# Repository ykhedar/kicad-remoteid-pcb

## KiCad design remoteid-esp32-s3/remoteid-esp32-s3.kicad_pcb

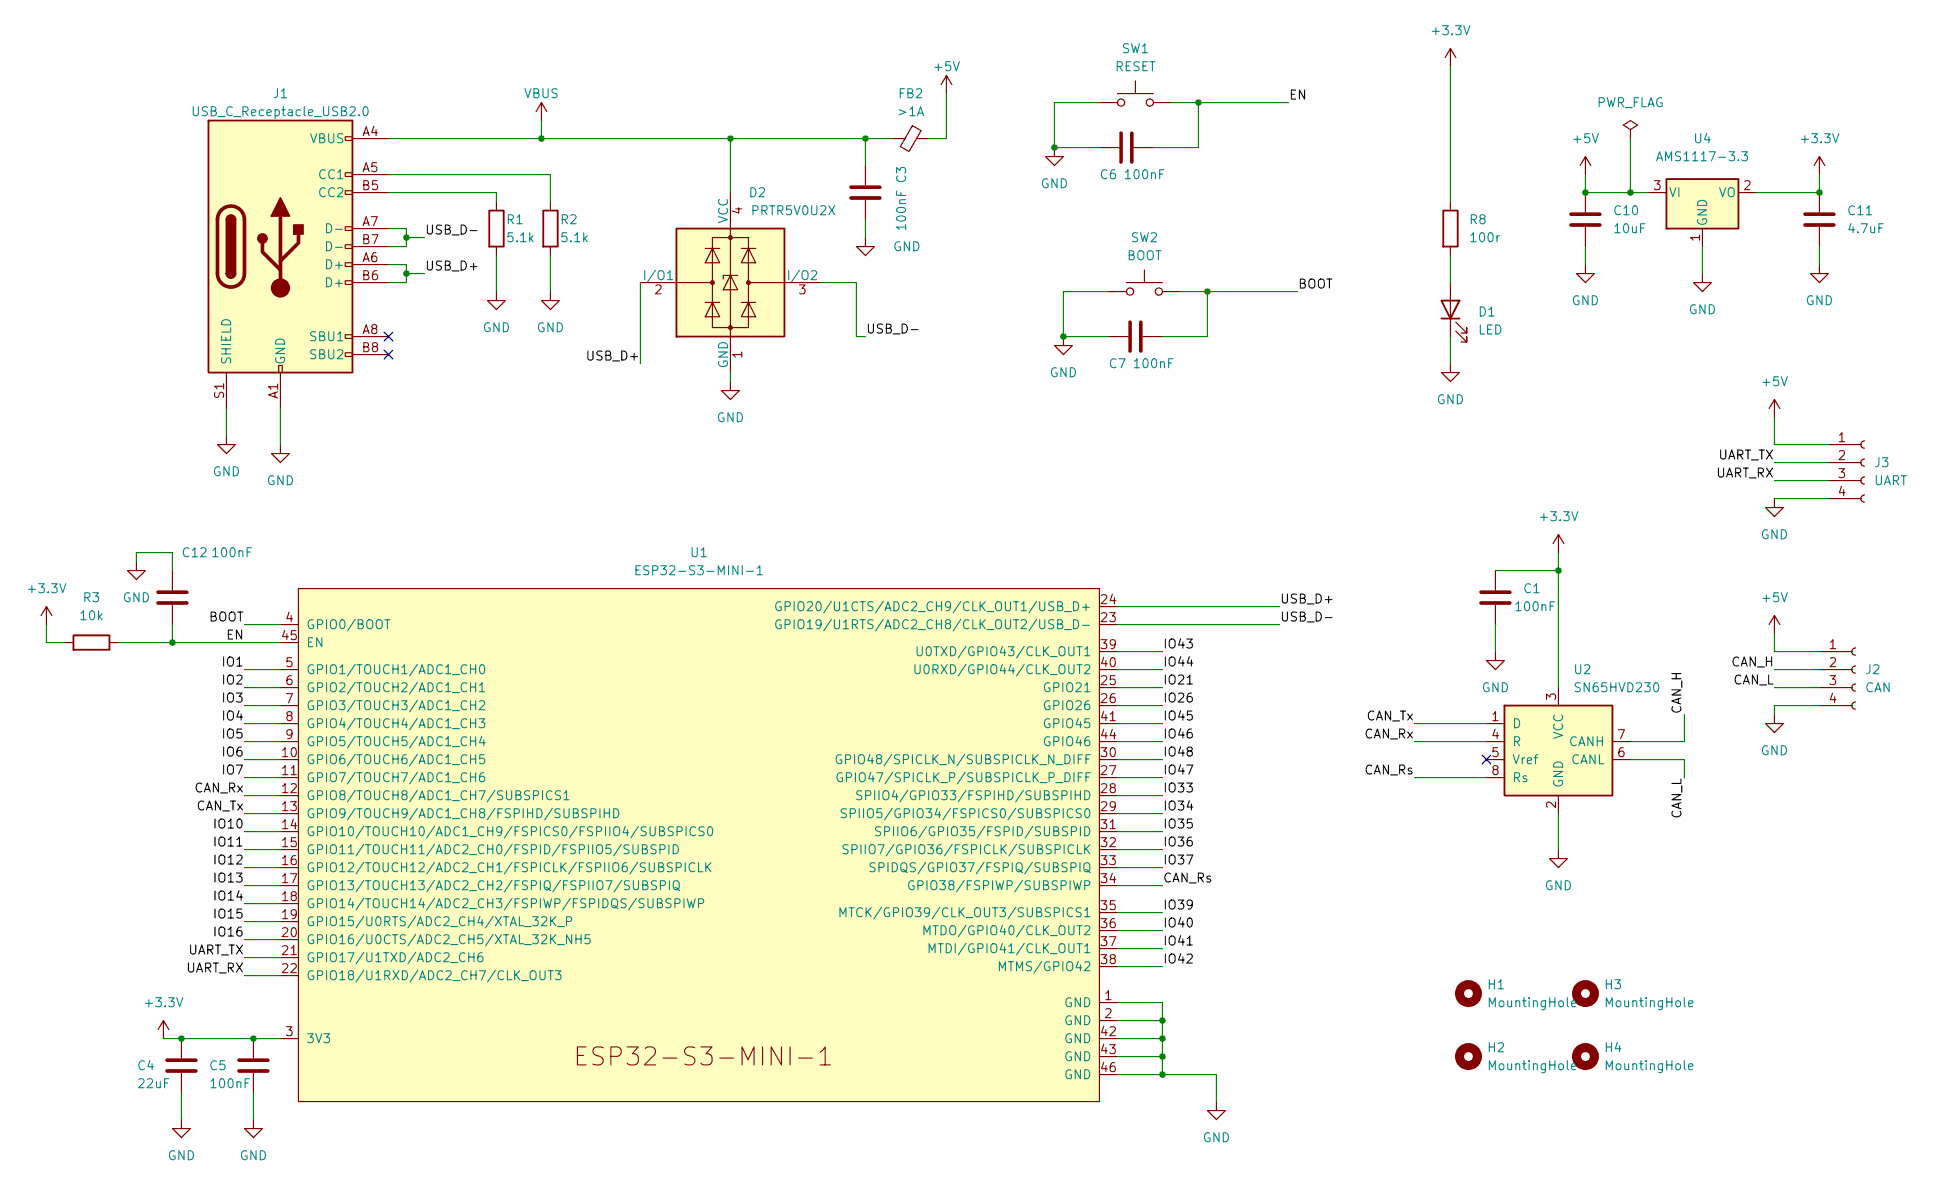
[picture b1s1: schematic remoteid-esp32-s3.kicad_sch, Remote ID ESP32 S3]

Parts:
C1, C12: 100nF; C_0805_2012Metric
C3, C5, C6, C7: 100nF; C_0805_2012Metric; MPN C14663; LCSC C14663
C4: 22uF; C_0805_2012Metric
C10: 10uF; C_0805_2012Metric
C11: 4.7uF; C_0805_2012Metric
D1: LED; LED_0603_1608Metric; MPN C205445; LCSC C205445
D2: PRTR5V0U2X; SOT-143
FB2: >1A; C_0603_1608Metric; MPN C85831; LCSC C85831
H1, H2, H3, H4: MountingHole; MountingHole_2.7mm_M2.5
J1: USB_C_Receptacle_USB2.0; USB_C_Receptacle_Palconn_UTC16-G; MPN C165948; LCSC C165948
J2: CAN; JST_GH_SM04B-GHS-TB_1x04-1MP_P1.25mm_Horizontal
J3: UART; JST_GH_SM04B-GHS-TB_1x04-1MP_P1.25mm_Horizontal
R1, R2: 5.1k; R_0603_1608Metric
R3: 10k; R_0603_1608Metric
R8: 100r; R_0603_1608Metric
SW1: RESET; Alps_SKRK; MPN C115357; LCSC C115357
SW2: BOOT; Alps_SKRK; MPN C115357; LCSC C115357
U1: ESP32-S3-MINI-1; ESP32-S3-MINI-1U; MPN C2980299; LCSC C2980299
U2: SN65HVD230; SOIC-8_3.9x4.9mm_P1.27mm; MPN C12084; LCSC C12084
U4: AMS1117-3.3; SOT-223-3_TabPin2; MPN C6186; LCSC C6186

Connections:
+3.3V: C1.1, C4.1, C5.1, C11.1, R3.2, R8.1, U1.3 (3V3), U2.3 (VCC), U4.2 (VO)
+5V: C10.1, FB2.1, J2.1, J3.1, U4.3 (VI)
/BOOT: C7.1, SW2.2, U1.4 (GPIO0/BOOT)
/CAN_H: J2.2, U2.7 (CANH)
/CAN_L: J2.3, U2.6 (CANL)
/CAN_Rs: U1.34 (GPIO38/FSPIWP/SUBSPIWP), U2.8 (Rs)
/CAN_Rx: U1.12 (GPIO8/TOUCH8/ADC1_CH7/SUBSPICS1), U2.4 (R)
/CAN_Tx: U1.13 (GPIO9/TOUCH9/ADC1_CH8/FSPIHD/SUBSPIHD), U2.1 (D)
/EN: C6.1, C12.2, R3.1, SW1.2, U1.45 (EN)
/IO1: U1.5 (GPIO1/TOUCH1/ADC1_CH0)
/IO2: U1.6 (GPIO2/TOUCH2/ADC1_CH1)
/IO3: U1.7 (GPIO3/TOUCH3/ADC1_CH2)
/IO4: U1.8 (GPIO4/TOUCH4/ADC1_CH3)
/IO5: U1.9 (GPIO5/TOUCH5/ADC1_CH4)
/IO6: U1.10 (GPIO6/TOUCH6/ADC1_CH5)
/IO7: U1.11 (GPIO7/TOUCH7/ADC1_CH6)
/IO10: U1.14 (GPIO10/TOUCH10/ADC1_CH9/FSPICS0/FSPIIO4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)
/IO11: U1.15 (GPIO11/TOUCH11/ADC2_CH0/FSPID/FSPIIO5/S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)
/IO12: U1.16 (GPIO12/TOUCH12/ADC2_CH1/FSPICLK/FSPIIO6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)
/IO13: U1.17 (GPIO13/TOUCH13/ADC2_CH2/FSPIQ/FSPIIO7/S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)
/IO14: U1.18 (GPIO14/TOUCH14/ADC2_CH3/FSPIWP/FSPIDQS/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)
/IO15: U1.19 (GPIO15/U0RTS/ADC2_CH4/XTAL_32K_P)
/IO16: U1.20 (GPIO16/U0CTS/ADC2_CH5/XTAL_32K_NH5)
/IO21: U1.25 (GPIO21)
/IO26: U1.26 (GPIO26)
/IO33: U1.28 (SPIIO4/GPIO33/FSPIHD/SUBSPIHD)
/IO34: U1.29 (SPIIO5/GPIO34/FSPICS0/SUBSPICS0)
/IO35: U1.31 (SPIIO6/GPIO35/FSPID/SUBSPID)
/IO36: U1.32 (SPIIO7/GPIO36/FSPICLK/SUBSPICLK)
/IO37: U1.33 (SPIDQS/GPIO37/FSPIQ/SUBSPIQ)
/IO39: U1.35 (MTCK/GPIO39/CLK_OUT3/SUBSPICS1)
/IO40: U1.36 (MTDO/GPIO40/CLK_OUT2)
/IO41: U1.37 (MTDI/GPIO41/CLK_OUT1)
/IO42: U1.38 (MTMS/GPIO42)
/IO43: U1.39 (U0TXD/GPIO43/CLK_OUT1)
/IO44: U1.40 (U0RXD/GPIO44/CLK_OUT2)
/IO45: U1.41 (GPIO45)
/IO46: U1.44 (GPIO46)
/IO47: U1.27 (GPIO47/SPICLK_P/SUBSPICLK_P_DIFF)
/IO48: U1.30 (GPIO48/SPICLK_N/SUBSPICLK_N_DIFF)
/UART_RX: J3.3, U1.22 (GPIO18/U1RXD/ADC2_CH7/CLK_OUT3)
/UART_TX: J3.2, U1.21 (GPIO17/U1TXD/ADC2_CH6)
/USB_D+: D2.2 (I/O1), J1.A6 (D+), J1.B6 (D+), U1.24 (GPIO20/U1CTS/ADC2_CH9/CLK_OUT1/USB_D+)
/USB_D-: D2.3 (I/O2), J1.A7 (D-), J1.B7 (D-), U1.23 (GPIO19/U1RTS/ADC2_CH8/CLK_OUT2/USB_D-)
GND: C1.2, C3.1, C4.2, C5.2, C6.2, C7.2, C10.2, C11.2, C12.1, D1.1 (K), D2.1 (GND), J1.A1 (GND), J1.A12 (GND), J1.B1 (GND), J1.B12 (GND), J1.S1 (SHIELD), J2.4, J3.4, R1.2, R2.2, SW1.1, SW2.1, U1.1 (GND), U1.2 (GND), U1.42 (GND), U1.43 (GND), U1.46 (GND), U2.2 (GND), U4.1 (GND)
unnamed: D1.2 (A), R8.2
unnamed: J1.A5 (CC1), R2.1
unnamed: J1.B5 (CC2), R1.1
VBUS: C3.2, D2.4 (VCC), FB2.2, J1.A4 (VBUS), J1.A9 (VBUS), J1.B4 (VBUS), J1.B9 (VBUS)

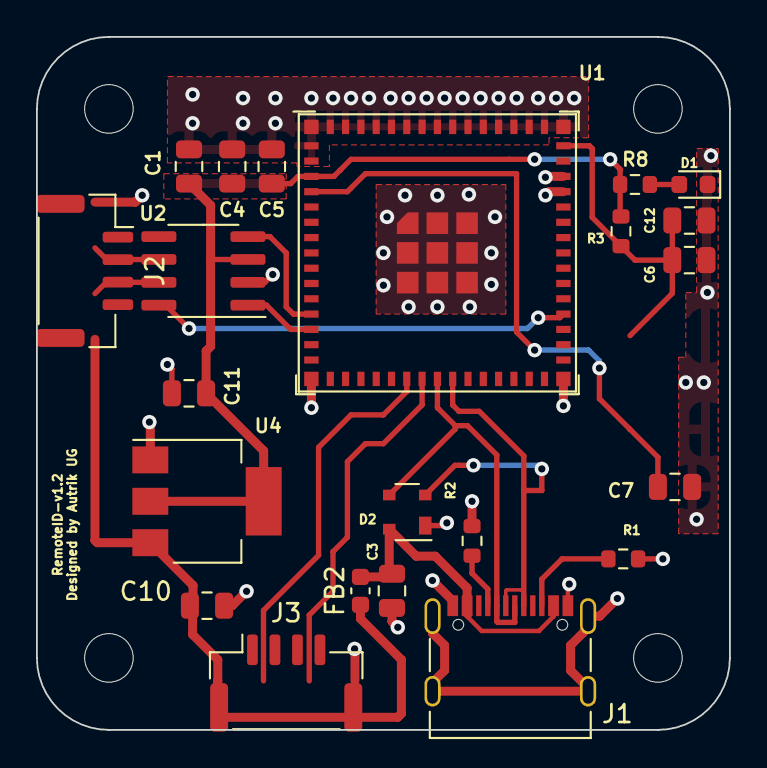
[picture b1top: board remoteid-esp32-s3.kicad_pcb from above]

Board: 2 copper layers, 38.5 x 38.5 mm, 26 parts (0 on the bottom side), 18 nets.
